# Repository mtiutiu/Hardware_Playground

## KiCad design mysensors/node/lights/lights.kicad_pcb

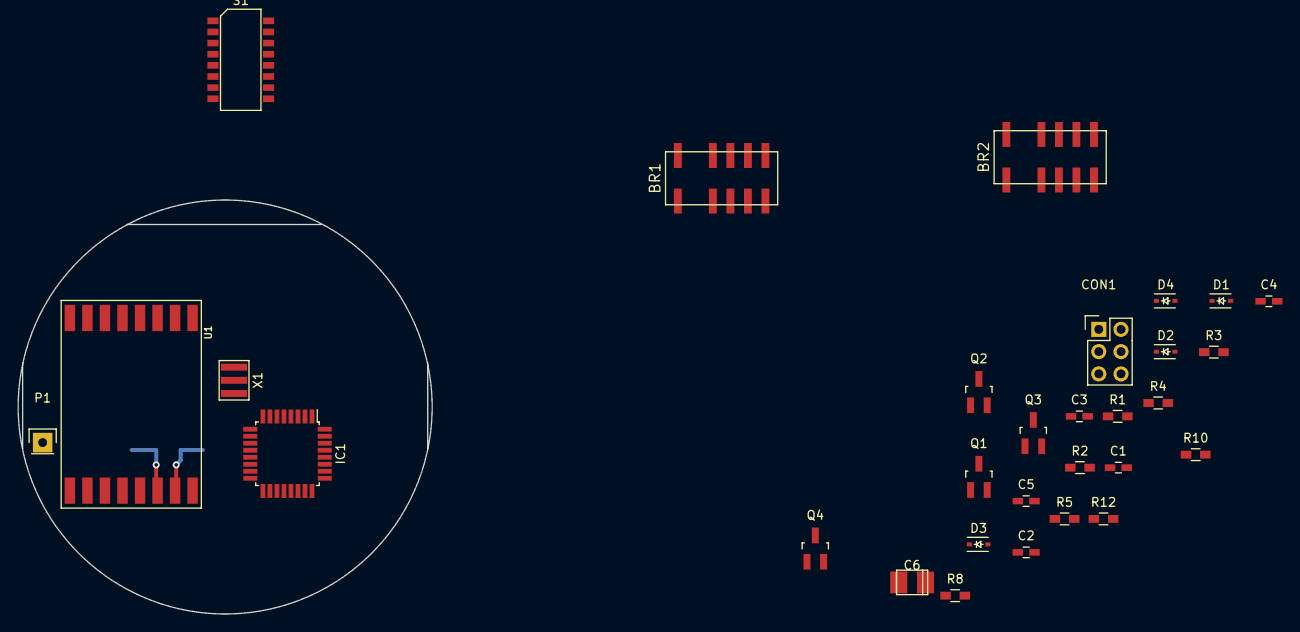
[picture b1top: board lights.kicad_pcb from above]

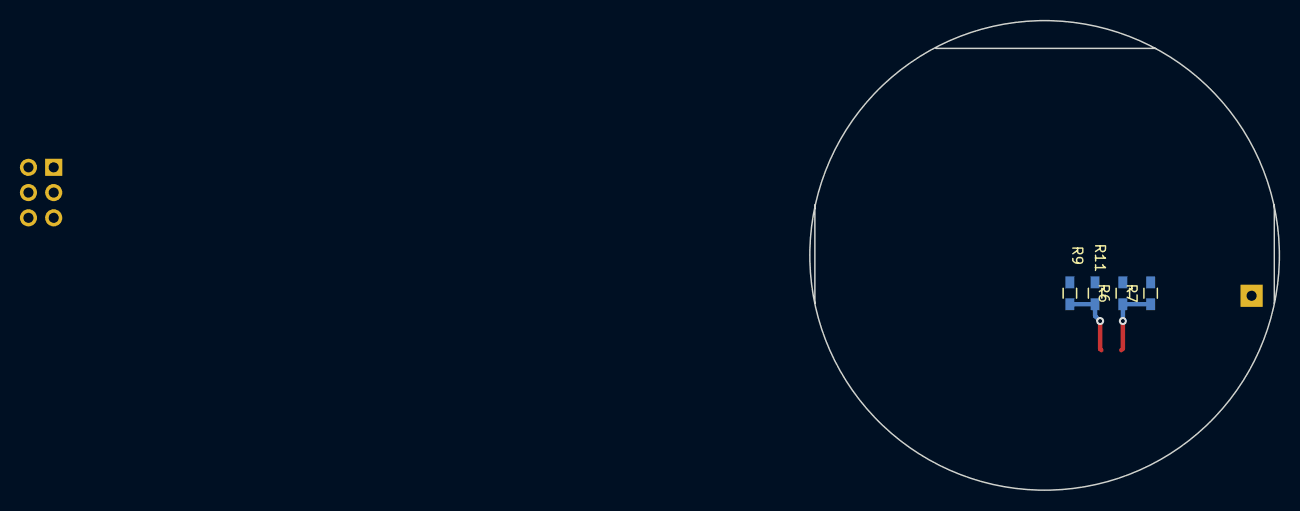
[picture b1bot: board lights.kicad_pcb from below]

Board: 2 copper layers, 47.2 x 47.2 mm, 34 parts (4 on the bottom side), 30 nets.

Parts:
BR1, BR2: V23079-E1208-B301
C1, C2, C3, C4, C5: 100n; C_0603_HandSoldering
C6: 10u; TantalC_SizeT_EIA-3528
CON1: AVR-ISP-6; Pin_Header_Straight_2x03
D1, D2, D3, D4: 1N4148; SOD-323
IC1: ATMEGA328P-A; TQFP-32_7x7mm_Pitch0.8mm
P1: ANTENNA; Pin_Header_Straight_1x01
Q1, Q2, Q3, Q4: 2n2222; SOT-23_Handsoldering
R1, R2, R3, R5: 5K6; R_0603_HandSoldering
R4: 10K; R_0603_HandSoldering
R6, R9, R10: 4K7; R_0603_HandSoldering
R7, R11, R12: 9K1; R_0603_HandSoldering
R8: 470; R_0603_HandSoldering
S1: MCDHA-08TQR; DIPSWITCH_SMD_1.27-16
U1: RFM69HW; RFM69HW_SMD_Handsoldering
X1: 8MHz; ZTTCR-3

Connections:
+3V3: BR1.7, BR1.12, BR2.7, BR2.12, C1.1, C2.2, C3.2, C6.1, CON1.2, D1.1, D2.1, D3.1, D4.1, IC1.4, IC1.6, IC1.18, R4.1, U1.8
/C0: IC1.1, S1.1
/C1: IC1.2, S1.2
/C2: IC1.9, S1.3
/C3: IC1.10, S1.4
/C4: IC1.11, S1.5
/C5: IC1.12, S1.6
/C6: IC1.13, S1.7
/INT: IC1.32, U1.2
/MISO: CON1.1, IC1.16, U1.13
/MOSI: CON1.4, IC1.15, R6.2
/RESET: C5.2, CON1.5, IC1.29, R4.2
/SCK: CON1.3, IC1.17, R10.2
/SS: IC1.14, R8.1, R9.2
GND: C1.2, C2.1, C3.1, C4.1, C5.1, C6.2, CON1.6, IC1.3, IC1.5, IC1.21, Q1.3, Q2.3, Q3.3, Q4.3, R7.2, R11.2, R12.2, S1.9, S1.10, S1.11, S1.12, S1.13, S1.14, S1.15, S1.16, U1.9, U1.11, X1.3
unnamed: BR1.1, D1.2, Q1.1
unnamed: BR1.6, D2.2, Q2.1
unnamed: BR2.1, D3.2, Q3.1
unnamed: BR2.6, D4.2, Q4.1
unnamed: C4.2, IC1.20
unnamed: IC1.7, X1.2
unnamed: IC1.8, X1.1
unnamed: P1.1, U1.10
unnamed: Q1.2, R1.1
unnamed: Q2.2, R2.1
unnamed: Q3.2, R3.1
unnamed: Q4.2, R5.1
unnamed: R6.1, R7.1, U1.14
unnamed: R10.1, R12.1, U1.12
unnamed: R9.1, R11.1, U1.15

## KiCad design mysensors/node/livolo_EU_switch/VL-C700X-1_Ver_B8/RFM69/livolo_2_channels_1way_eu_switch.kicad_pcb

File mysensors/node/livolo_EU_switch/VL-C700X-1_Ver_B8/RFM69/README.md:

## Mysensors RFM69 Livolo 2 channels 1 way EU switch front module
More details here: https://www.openhardware.io/view/306

##### 3D renderings of pcb

Top view | Bottom view
------------ | -------------
 | 

**Description:**

This is a Mysensors replica of the Livolo EU Switch(2 channels 1 way) front plate for the **VL-C700X-1_Ver_B8** Livolo hw revision.

**Key Features:**

 - **Capacitive touch sensing** using **TTP223** specialized IC
 - **AT25DF512C-SSHN-B** SPI flash module for OTA
 - **ATSHA204A** for signing
 - **MySensors** ready(Atmega328p + RFM69CW)
 - **DC-DC Buck converter** in combination with a **linear LDO voltage regulator** for efficient **noise cancelling**
  (the used LDO reduces a little bit the Buck's converter current capability - down to 150mA from 600mA but this is not important as the whole board takes about 60mA at peak)

**Work progress:**
 1. Identify the 12V line from the Livolo power/relays board - **DONE**
 2. Add **AT25DF512C-SSHN-B** SPI Flash module for OTA and **ATSHA204A** for signing - **DONE**
 3. Test/verify the pcb board correctness(from both electrical and mechanical point of views) - **DONE**
 4. Produce the initial PCB's using some external PCB manufacturer - **DONE**
 5. Components assembly(soldering) - **DONE**
 6. Create Mysensors sketch code - **DONE**
 7. Verify the real board with running code - **DONE**
 8. Verify OTA - **DONE**

Regarding point 1. from above: the EU variant that I have(VL-C700X-1 Ver: B8) doesn't expose the 12V line unfortunately. So I see 2 options here:

1. Bypass the 3V regulator from the power supply/relays board completely so that I get 12V directly to my board
2. ~~Find a free(if available) pin on the 2x6 pin connector and solder a wire to that pin from the 12V line(this requires less intervention)~~

One another thing that I noticed is that the relays are bistable so I modified the schematic/pcb to accommodate that(the relays used on my livolo switch are: **HFE60 12-1HST-L2** ( **2 coils latching, 1 Form A** as per datasheet: http://www.hongfa.com/pro/pdf/HFE60_en.pdf).

**HW Revisions:**
 - 0.1 - added SPI flash for OTA and signing support
 - 0.2 - fixed SPI slave select lines for flash and radio module
 - 0.3 - added ATSHA204A pull-up resistor
 - 0.4 - fixed leds orientation and added touch pads silkscreen
 - 0.5 - added tantalum caps for better power supply and radio stability(removed MCU reset pin cap)

The only thing I ask if using this project is to at least mention my name and if I don't ask too much you can also support my effort using the below button. Thanks.

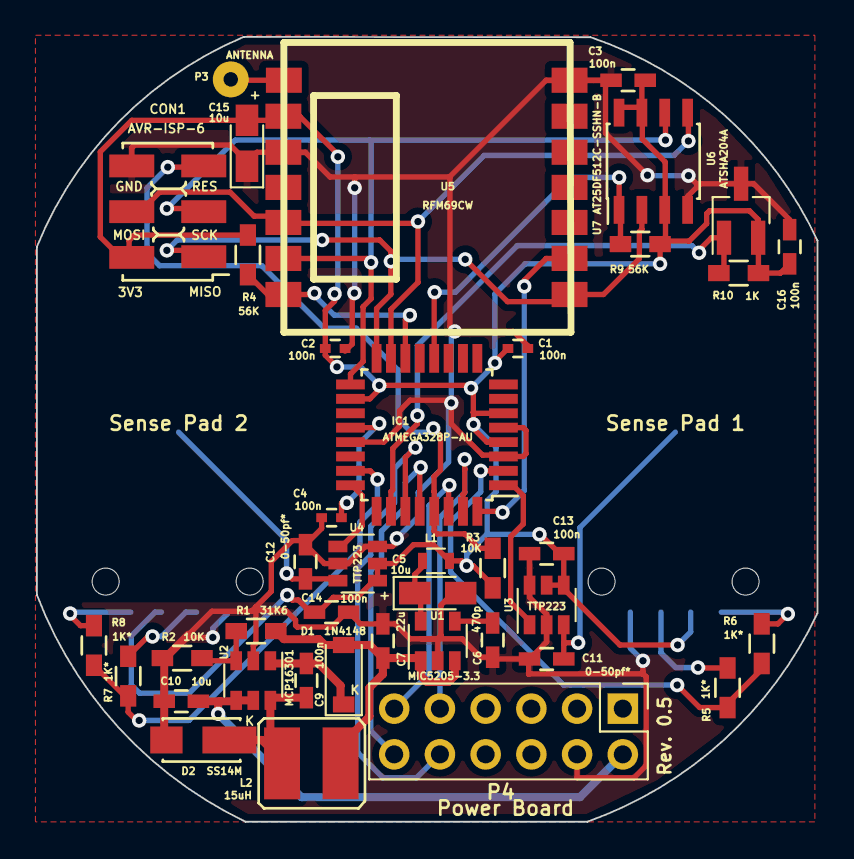
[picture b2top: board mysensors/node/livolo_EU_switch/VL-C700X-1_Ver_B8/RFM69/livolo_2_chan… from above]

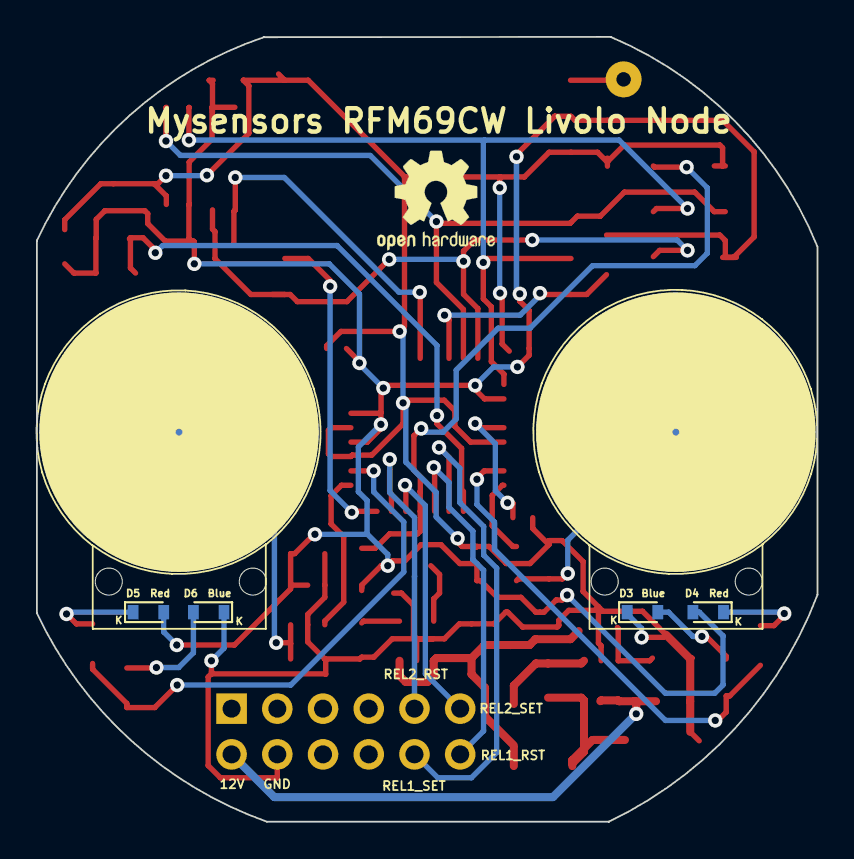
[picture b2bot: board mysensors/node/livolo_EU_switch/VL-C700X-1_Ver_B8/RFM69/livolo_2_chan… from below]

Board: 2 copper layers, 43.4 x 43.6 mm, 46 parts (4 on the bottom side), 33 nets.

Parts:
C1, C2, C4: 100n; C_0402
C3, C9, C13, C14, C16: 100n; C_0603_HandSoldering
C5, C15: 10u; CP_Tantalum_Case-R_EIA-2012-12_Wave
C6: 470p; C_0603_HandSoldering
C7: 22u; C_0603_HandSoldering
C10: 10u; C_0603_HandSoldering
C11, C12: 0-50pf*; C_0603_HandSoldering
CON1: AVR-ISP-6; AVR_ISP_SMT_Small_02x03
D1: 1N4148; SOD-123
D2: SS14M
D3, D6: Blue; D_0603
D4, D5: Red; D_0603
IC1: ATMEGA328P-AU; TQFP-32_7x7mm_Pitch0.8mm
L1: BLM18HE152SN1D; R_0603
L2: 15uH; VLCF4020T-150MR68
P1: Sense Pad 1; touch_pad_16mm
P2: Sense Pad 2; touch_pad_16mm
P3: ANTENNA; SolderWirePad_single_0-8mmDrill
P4: Power Board; Pin_Header_Straight_2x06_Pitch2.54mm
R1: 31K6; R_0603_HandSoldering
R2, R3: 10K; R_0603_HandSoldering
R4, R9: 56K; R_0603_HandSoldering
R5, R6, R7, R8: 1K*; R_0603_HandSoldering
R10: 1K; R_0603_HandSoldering
U1: MIC5205-3.3; SOT-23-5
U2: MCP16301; SOT-23-6
U3, U4: TTP223; SOT-23-6
U5: RFM69CW
U6: AT25DF512C-SSHN-B; SOIC-8_3.9x4.9mm_Pitch1.27mm
U7: ATSHA204A; SOT-23_Handsoldering

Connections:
+3V3: C1.1, C2.2, C3.2, C13.1, C14.1, C15.2, C16.2, CON1.2, D4.2, D5.2, IC1.4, IC1.6, IC1.18, L1.1, R3.1, R4.2, R9.1, R10.1, U3.4, U3.5, U4.4, U4.5, U5.2, U6.3, U6.7, U6.8, U7.2
/12Vcc: C10.1, P4.2, U2.4, U2.5
/ATSHA204A: IC1.26, R10.2, U7.1
/FLASH_SS: IC1.12, R9.2, U6.1
/INT: IC1.32, U5.9
/MISO: CON1.1, IC1.16, U5.8, U6.2
/MOSI: CON1.4, IC1.15, U5.5, U6.5
/RADIO_SS: IC1.14, R4.1, U5.7
/RESET: CON1.5, IC1.29, R3.2
/Relay1_Reset: IC1.28, P4.12
/Relay1_Set: IC1.27, P4.10
/Relay2_Reset: IC1.31, P4.9
/Relay2_Set: IC1.30, P4.11
/S1_LEDs: IC1.2, R5.2, R6.2
/S2_LEDs: IC1.23, R7.2, R8.2
/SCK: CON1.3, IC1.17, U5.6, U6.6
/TS1: IC1.1, U3.1
/TS2: IC1.24, U4.1
GND: C1.2, C2.1, C3.1, C4.1, C5.2, C6.2, C7.2, C10.2, C11.2, C12.2, C13.2, C14.2, C15.1, C16.1, CON1.6, D2.2, D3.1, D6.1, IC1.3, IC1.5, IC1.21, P4.4, R2.1, U1.2, U2.2, U3.2, U3.6, U4.2, U4.6, U5.3, U5.14, U6.4, U7.3
unnamed: C4.2, IC1.20
unnamed: C5.1, L1.2, U1.5
unnamed: C6.1, U1.4
unnamed: C7.1, D1.2, L2.1, R1.2, U1.1, U1.3
unnamed: C9.1, D1.1, U2.1
unnamed: C9.2, D2.1, L2.2, U2.6
unnamed: C11.1, P1.1, U3.3
unnamed: C12.1, P2.1, U4.3
unnamed: D3.2, R7.1
unnamed: D4.1, R8.1
unnamed: D5.1, R6.1
unnamed: D6.2, R5.1
unnamed: P3.1, U5.1
unnamed: R1.1, R2.2, U2.3

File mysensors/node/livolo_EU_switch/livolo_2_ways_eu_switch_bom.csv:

Component,Description,Part,References,Value,Footprint,Quantity Per PCB,Datasheet,Rating,Vendor,Part No
1,Unpolarized capacitor,C_Small,C11 C12,0-50pf*,C_0603_HandSoldering,2,http://www.farnell.com/datasheets/1825496.pdf,C0G/25V,Multicomp,MCMT18N100F250CT
2,Unpolarized capacitor,C_Small,C1 C2 C4,100n,C_0402,3,http://www.farnell.com/datasheets/1870456.pdf,X5R/25V,Multicomp,MC0402X104K250CT
3,Unpolarized capacitor,C_Small,C3 C9 C13 C14 C16,100n,C_0603_HandSoldering,5,http://www.farnell.com/datasheets/1901289.pdf,X7R/25V,Multicomp,MC0603B104K250CT
4,Unpolarized capacitor,C_Small,C10,10u,C_0603_HandSoldering,1,http://www.farnell.com/datasheets/2163235.pdf,X5R/25V,Murata,ZRB18AR61E106ME01L
5,Polarised capacitor,CP1_Small,C5 C15,10u,CP_Tantalum_Case-R_EIA-2012-12_Wave,2,http://www.farnell.com/datasheets/1955682.pdf,X5R/10V,Murata,GRM188R61A106KE69D
6,Unpolarized capacitor,C_Small,C7,22u,C_0603_HandSoldering,1,http://www.farnell.com/datasheets/2047978.pdf,X5R/10V,Murata,GRM188R61A226ME15D
7,Unpolarized capacitor,C_Small,C6,470p,C_0603_HandSoldering,1,http://www.farnell.com/datasheets/1870456.pdf,X7R/25V,Multicomp,MC0603B103K250CT
8,"Standard IDC6 Male Connector, ATMEL ISP 6pin",AVR-ISP-6,CON1,AVR-ISP-6,AVR_ISP_SMT_Small_02x03,1,,,,
9,"Diode, small symbol",D_Small,D1,1N4148,SOD-123,1,http://www.farnell.com/datasheets/2099776.pdf,100V/300mA,Diodes Inc.,1N4148W-7-F
10,"LED, small symbol",LED_Small,D3 D6,Blue,D_0603,2,http://www.tme.eu/ro/Document/2ff6cd49d353fcb76ded3ea208e0eb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,2.5-3.4V/5mA,Optosupply,OSB50603C1E
11,"LED, small symbol",LED_Small,D4 D5,Red,D_0603,2,http://www.tme.eu/ro/Document/2ff6cd49d353fcb76ded3ea208e0eb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,1.6-2.4V/5mA,Optosupply,OSR50603C1E
12,"Schottky diode, small symbol",D_Schottky_Small,D2,SS14M,SS14M,1,http://www.farnell.com/datasheets/1692176.pdf,40V/1A,Taiwan Semiconductor,SS14M
13,"TQFP32, 16k Flash, 1kB SRAM, 512B EEPROM",ATMEGA328P-AU,IC1,ATMEGA328P-AU,TQFP-32_7x7mm_Pitch0.8mm,1,http://www.atmel.com/images/atmel-8271-8-bit-avr-microcontro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,,,
14,"Inductor, small symbol",L_Small,L2,15uH,VLCF4020T-150MR68,1,http://www.farnell.com/datasheets/2041203.pdf,1A,TDK,VLCF4020T-150MR68
15,"Inductor, small symbol",L_Small,L1,BLM18HE152SN1D,R_0603,1,http://www.murata.com/en-us/products/productdata/87967415992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,,,
17,"Connector, double row, 02x06, pin header",CONN_02X06,P4,Power Board,Pin_Header_Straight_2x06_Pitch2.54mm,1,http://www.tme.eu/ro/Document/dd1ceac14413aeeec818bc9967f247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,,Ninigi,ZL262-12DG
20,"Resistor, small symbol",R_Small,R2 R3,10K,R_0603_HandSoldering,2,http://www.farnell.com/datasheets/2007183.pdf,50V/200mW,TE Connectivity,CRGH0603J10K
21,"Resistor, small symbol",R_Small,R10,1K,R_0603_HandSoldering,1,http://www.farnell.com/datasheets/1849611.pdf,50V/100mW,Multicomp,MCWR06X5602FTL
22,"Resistor, small symbol",R_Small,R5 R6 R7 R8,1K*,R_0603_HandSoldering,4,http://www.farnell.com/datasheets/1849611.pdf,50V/100mW 50V/200mW,Multicomp,MCWR06X1001FTL
23,"Resistor, small symbol",R_Small,R1,31K6,R_0603_HandSoldering,1,http://www.farnell.com/datasheets/1849611.pdf,50V/200mW,Multicomp,MCWR06X3162FTL
24,"Resistor, small symbol",R_Small,R4 R9,56K,R_0603_HandSoldering,2,http://www.farnell.com/datasheets/2007183.pdf,50V/200mW 50V/100mW,TE Connectivity Multicomp,CRGH0603J10K MCWR06X5602FTL
25,"AT25DF512C, 512-Kbit SPI Serial Flash Memory, SOIC-8, Vcc=3.3V",AT25DF512C,U6,AT25DF512C-SSHN-B,SOIC-8_3.9x4.9mm_Pitch1.27mm,1,http://www.adestotech.com/wp-content/uploads/DS-AT25DF512C-030.pdf,,,
26,"ATSHA204A, Secure Authentication and Validation Device, SOT-23, Vcc=3.3V",ATSHA204A,U7,ATSHA204A,SOT-23_Handsoldering,1,http://www.atmel.com/Images/Atmel-8885-CryptoAuth-ATSHA204A-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,,,
27,"4.0 to 30V Input, 1A output, integrated switch step-down regulator, SOT-23-6 package",MCP16301,U2,MCP16301,SOT-23-6,1,http://www.farnell.com/datasheets/2129968.pdf,4-30V/3.3V/600mA,Microchip,MCP16301T-I/CHY
28,,MIC5205-3.3YM5TR,U1,MIC5205-3.3,SOT-23-5,1,http://www.farnell.com/datasheets/29605.pdf,3.3V/150mA,Microchip,MIC5205-3.3YM5-TR
29,,RFM69CW,U5,RFM69CW,RFM69CW,1,http://www.hoperf.com/upload/rf/RFM69CW-V1.1.pdf,3.3V/868MHz,HopeRF,RFM69CW
30,,TTP223,U3 U4,TTP223,SOT-23-6,2,http://www.coldtears-electronics.com/images/TTP223.pdf,,Tontek,
,,,,,,,,,,
,,,,,,,,,,
,,,,,,,,,,
,,,,,,,,,,
,,,,,,,,,,
Component Groups:,30,,,,,,,,,
Component Count:,43,,,,,,,,,
Fitted Components:,43,,,,,,,,,
Number of PCBs:,1,,,,,,,,,
Total components:,43,,,,,,,,,
Schematic Version:,0.5,,,,,,,,,
Schematic Date:,,,,,,,,,,
BoM Date:,Mon 13 Mar 2017 05:45:51 PM EET,,,,,,,,,
Schematic Source:,/home/mtiutiu/Work/kicad/mysensors/node/livolo_EU_switch/livolo_2_ways_eu_switch.sch,,,,,,,,,
KiCad Version:,Eeschema no-vcs-found-5e5259b~58~ubuntu16.04.1,,,,,,,,,

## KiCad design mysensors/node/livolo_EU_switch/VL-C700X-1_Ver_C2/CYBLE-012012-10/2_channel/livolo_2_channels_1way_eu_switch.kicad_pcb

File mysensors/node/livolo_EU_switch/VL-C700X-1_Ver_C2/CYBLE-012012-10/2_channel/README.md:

## Mysensors PSOC PROC BLE (CYBLE-012012-10) Livolo 2 channels 1 way EU switch front module

##### 3D renderings of pcb

Top view | Bottom view
------------ | -------------
 | 

If this project was of any help you can buy me a beer or at least support my effort by using the below button. Thanks.

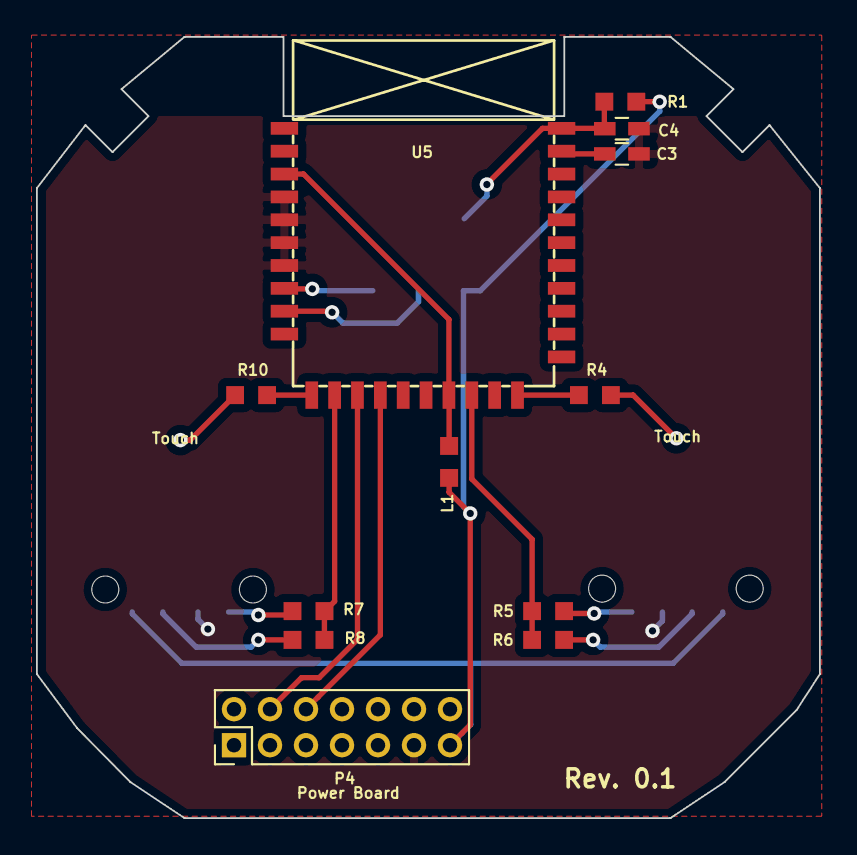
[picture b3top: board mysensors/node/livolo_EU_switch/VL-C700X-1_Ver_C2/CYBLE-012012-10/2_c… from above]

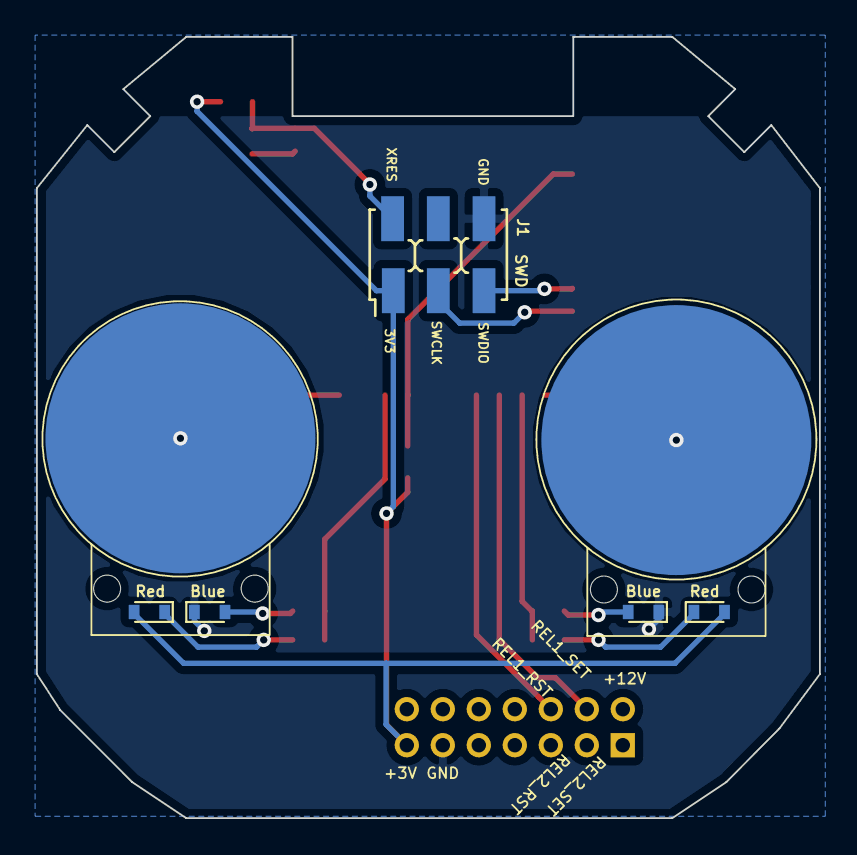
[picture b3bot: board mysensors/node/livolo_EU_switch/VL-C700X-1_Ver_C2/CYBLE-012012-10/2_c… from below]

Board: 2 copper layers, 43.5 x 43.4 mm, 19 parts (5 on the bottom side), 21 nets.

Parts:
C3: 2n2; C_0603_HandSoldering
C4: 100p; C_0603_HandSoldering
D3, D6: Blue; D_0603
D4, D5: Red; D_0603
J1: SWD; AVR_ISP_SMT_Small_02x03
L1: 300ohm/100Mhz; R_0603_1608Metric_Pad0.99x1.00mm_HandSolder
P4: Power Board; Pin_Header_Straight_2x07_Pitch2.00mm
R1, R4, R10: 4K7; R_0603_1608Metric_Pad0.99x1.00mm_HandSolder
R5, R6, R7, R8: 1K*; R_0603_1608Metric_Pad0.99x1.00mm_HandSolder
U1: Touch; livolo_ts_guard_cut_left
U5: CYBLE-012012-10
U6: Touch; livolo_ts_guard_cut_right

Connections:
+3V3: D4.2, D5.2, J1.1, L1.1, P4.13, R1.2
/Relay1_Reset: P4.6, U5.18
/Relay1_Set: P4.4, U5.19
/Relay2_Reset: P4.3, U5.17
/Relay2_Set: P4.5, U5.16
/S1_LEDs: R5.2, R6.2, U5.14
/S2_LEDs: R7.2, R8.2, U5.20
/SWCLK: J1.3, U5.23
/SWDIO: J1.5, U5.24
/TS1: R10.2, U5.21
/TS2: R4.1, U5.12
/XRES: C4.1, J1.2, R1.1, U5.1
GND: C3.1, C4.2, D3.1, D6.1, J1.6, P4.11, U5.25, U5.26, U5.27, U5.28
unnamed: C3.2, U5.2
unnamed: D3.2, R7.1
unnamed: D4.1, R8.1
unnamed: D5.1, R6.1
unnamed: D6.2, R5.1
unnamed: L1.2, U5.15, U5.29
unnamed: R4.2, U6.1
unnamed: R10.1, U1.1

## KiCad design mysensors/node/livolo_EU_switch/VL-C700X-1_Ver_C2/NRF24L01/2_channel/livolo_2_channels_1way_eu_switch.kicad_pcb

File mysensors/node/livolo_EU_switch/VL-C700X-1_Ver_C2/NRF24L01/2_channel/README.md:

## Mysensors NRF24L01 Livolo 2 channels 1 way EU switch front module

##### 3D renderings of pcb

Top view | Bottom view
------------ | -------------
 | 

**Description:**

This is a Mysensors replica of the Livolo EU Switch(2 channels 1 way) front plate for the **VL-C702X-2_Ver_C1** Livolo hw revision.

**Key Features:**

 - **Capacitive touch sensing** using **MTCH105** specialized IC
 - **ATSHA204A** for signing
 - **MCP9700** for temperature sensing
 - **MySensors** ready(Atmega328p + NRF24L01)

**Work progress:**
 1. Test/verify the pcb board correctness(from both electrical and mechanical point of views) - **DONE**
 2. Produce the initial PCB's using some external PCB manufacturer - **IN PROGRESS**
 3. Components assembly(soldering)
 4. Create Mysensors sketch code
 5. Verify the real board with running code
 6. Verify OTA

**HW Revisions:**
 - 0.1 - initial hw design
 - 0.2 - switched to MTCH105 touch IC and added temperature sensor

If this project was of any help you can buy me a beer or at least support my effort by using the below button. Thanks.

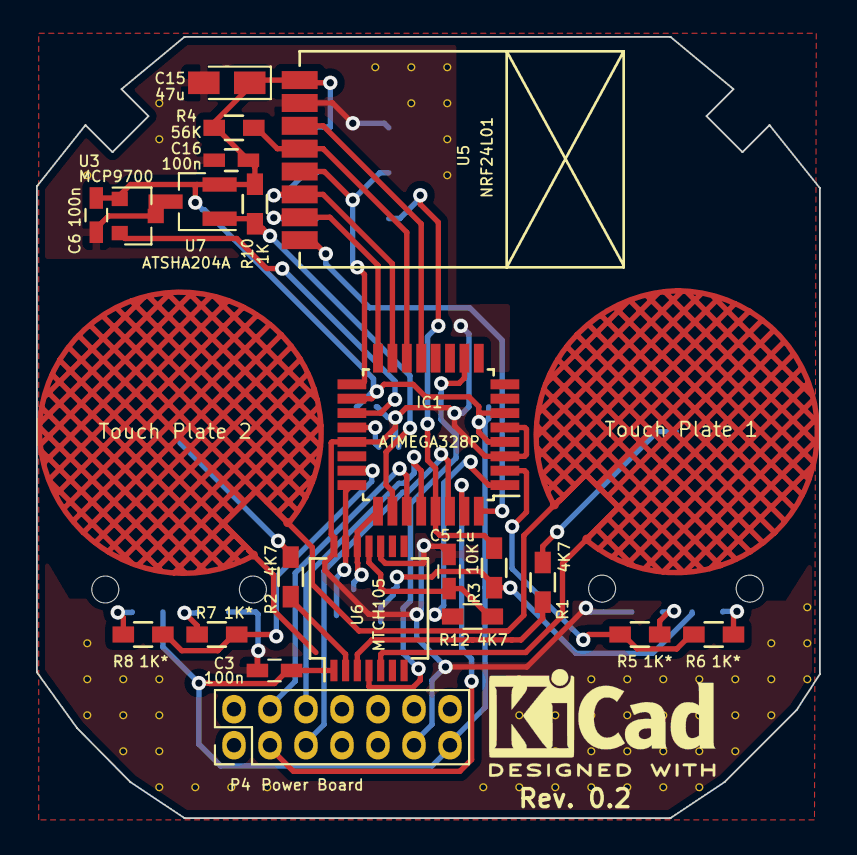
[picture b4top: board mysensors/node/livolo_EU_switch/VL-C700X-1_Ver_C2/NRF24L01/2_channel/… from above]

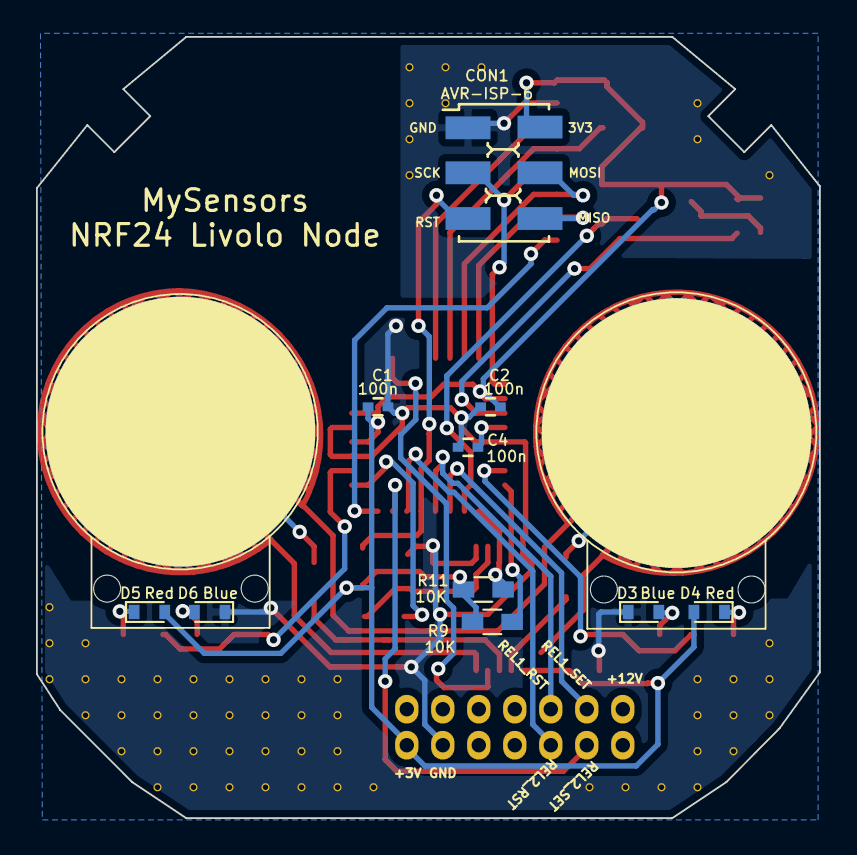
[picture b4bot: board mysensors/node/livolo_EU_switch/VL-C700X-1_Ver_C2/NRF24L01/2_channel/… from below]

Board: 2 copper layers, 43.5 x 43.4 mm, 90 parts (10 on the bottom side), 32 nets.

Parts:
C1, C2, C4: 100n; C_0402
C3, C6, C16: 100n; C_0603_HandSoldering
C5: 1u; C_0603_HandSoldering
C15: 47u; CP_Tantalum_Case-R_EIA-2012-12_Wave
CON1: AVR-ISP-6; AVR_ISP_SMT_Small_02x03
D3, D6: Blue; D_0603
D4, D5: Red; D_0603
IC1: ATMEGA328P; TQFP-32_7x7mm_Pitch0.8mm
P4: Power Board; Pin_Header_Straight_2x07_Pitch2.00mm
R1, R2, R12: 4K7; R_0603_HandSoldering
R3, R9, R11: 10K; R_0603_HandSoldering
R4: 56K; R_0603_HandSoldering
R5, R6, R7, R8: 1K*; R_0603_HandSoldering
R10: 1K; R_0603_HandSoldering
U1: Touch Plate 2; livolo_ts_guard_cut_simple
U2: Touch Plate 1; livolo_ts_guard_cut_simple
U3: MCP9700; SOT-23
U5: NRF24L01; NRF24L01-SMD
U6: MTCH105; SSOP-14_5.3x6.2mm_Pitch0.65mm
U7: ATSHA204A; SOT-23_Handsoldering
V2_4, V2_17, V2_18, V2_19, V3_18, V3_19, V3_20, V4_2, V4_3, V4_18, V4_19, V4_20, V4_21, V5_21, V6_21, V7_21, V10_1, V11_1, V11_2, V12_1, V12_2, V12_3, V12_4, V13_21, V14_18, V14_19, V14_20, V14_21, V15_18, V15_19, V15_20, V15_21, V16_18, V16_19, V16_20, V16_21, V17_18, V17_19, V17_20, V17_21, V18_18, V18_19, V18_20, V18_21, V19_18, V19_19, V19_20, V19_21, V20_18, V20_19, V20_20, V21_17, V21_18, V21_19, V22_16, V22_17, V22_18: AUTO_VIA; VIA_MATRIX

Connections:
+3V3: C1.1, C2.2, C3.1, C6.2, C15.1, C16.2, CON1.2, D4.2, D5.2, IC1.4, IC1.6, IC1.18, P4.13, R3.1, R4.2, R9.1, R10.1, R11.1, U3.1, U5.2, U6.1, U7.2
/ATSHA204A: IC1.26, R10.2, U7.1
/MISO: CON1.6, IC1.16, U5.7
/MOSI: CON1.4, IC1.15, U5.6
/MTPM: IC1.10, U6.4
/MTSA: IC1.1, R12.1
/RADIO_CE: IC1.13, U5.3
/RADIO_CSN: IC1.14, R4.1, U5.4
/RADIO_IRQ: IC1.32, U5.8
/RESET: CON1.5, IC1.29, R3.2
/Relay1_Reset: IC1.28, P4.6
/Relay1_Set: IC1.27, P4.4
/Relay2_Reset: IC1.31, P4.3
/Relay2_Set: IC1.30, P4.5
/S1_LEDs: IC1.2, R5.2, R6.2
/S2_LEDs: IC1.23, R7.2, R8.2
/SCK: CON1.3, IC1.17, U5.5
/TEMP_SENS: IC1.19, U3.2
/TS1: IC1.24, R9.2, U6.13
/TS2: IC1.25, R11.2, U6.12
GND: C1.2, C2.1, C3.2, C4.1, C5.2, C6.1, C15.2, C16.1, CON1.1, D3.1, D6.1, IC1.3, IC1.5, IC1.21, P4.11, U3.3, U5.1, U6.10, U6.14, U7.3, V2_4.1, V2_17.1, V2_18.1, V2_19.1, V3_18.1, V3_19.1, V3_20.1, V4_2.1, V4_3.1, V4_18.1, V4_19.1, V4_20.1, V4_21.1, V5_21.1, V6_21.1, V7_21.1, V10_1.1, V11_1.1, V11_2.1, V12_1.1, V12_2.1, V12_3.1, V12_4.1, V13_21.1, V14_18.1, V14_19.1, V14_20.1, V14_21.1, V15_18.1, V15_19.1, V15_20.1, V15_21.1, V16_18.1, V16_19.1, V16_20.1, V16_21.1, V17_18.1, V17_19.1, V17_20.1, V17_21.1, V18_18.1, V18_19.1, V18_20.1, V18_21.1, V19_18.1, V19_19.1, V19_20.1, V19_21.1, V20_18.1, V20_19.1, V20_20.1, V21_17.1, V21_18.1, V21_19.1, V22_16.1, V22_17.1, V22_18.1
unnamed: C4.2, IC1.20
unnamed: C5.1, R12.2, U6.11
unnamed: D3.2, R7.1
unnamed: D4.1, R8.1
unnamed: D5.1, R6.1
unnamed: D6.2, R5.1
unnamed: R1.1, U6.3
unnamed: R1.2, U2.1
unnamed: R2.1, U1.1
unnamed: R2.2, U6.2
unnamed: U1.2, U2.2, U6.5

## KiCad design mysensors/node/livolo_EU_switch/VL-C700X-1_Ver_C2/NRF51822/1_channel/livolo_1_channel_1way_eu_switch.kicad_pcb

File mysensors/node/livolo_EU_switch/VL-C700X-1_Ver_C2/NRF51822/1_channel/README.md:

## Mysensors NRF51822 Livolo 1 channels 1 way EU switch front module

##### 3D renderings of pcb

Top view | Bottom view
------------ | -------------
 | 

**Description:**

This is a Mysensors replica of the Livolo EU Switch(1 channel 1 way) front plate for the **VL-C702X-2_Ver_C1** Livolo hw revision.

**Key Features:**

 - **Capacitive touch sensing** using **MTCH102** specialized IC
 - **MySensors** ready(NRF51822)
 - **DC-DC Buck converter** for powering from the 12V line ( the DC-DC converter can be bypassed and not used at all if desired by soldering the **3V_EN** jumper and removing the L1 ferrite bead or by not soldering the dc-dc converter components)

**Firmware programming and testing steps for MySensors:**
1. Install Arduino IDE
2. Install nrf5 arduino core from here: https://github.com/sandeepmistry/arduino-nRF5
3. Select the **nrf51 generic board (16K ram and 256K flash)** variant(or nrf52 generic if you have a nrf52832 device)
4. The low frequency oscillator needs to be set to **RC oscillator** in the Arduino menu
5. **NO Softdevice** needs to be selected
6. Use a st-link v2 programmer
7. You need to connect only: SWD, SWCLK, Vdd and GND
8. Load your MySensors sketch or use the one provided with this project 

**Firmware programming and testing steps for BLE:**
1. Install Arduino IDE
2. Install nrf5 arduino core from here: https://github.com/sandeepmistry/arduino-nRF5
3. install Arduino ble peripheral library from here: https://github.com/sandeepmistry/arduino-BLEPeripheral
4. Install the required softdevice as explained here: https://github.com/sandeepmistry/arduino-nRF5#selecting-a-softdevice
5. Select the **nrf51 generic board (16K ram and 256K flash)** variant(or nrf52 generic if you have a nrf52832 device)
6. The low frequency oscillator needs to be set to **RC oscillator** in the Arduino menu
7. Select **S130** softdevice from menu if you have nrf51(or S132 if you have nrf52)
8. Use a st-link v2 programmer
9. You need to connect only: SWD, SWCLK, Vdd and GND
10. Load my BLE testing sketch, compile and upload
11. Use the nrf connect tool for Android: https://play.google.com/store/apps/details?id=no.nordicsemi.android.mcp&hl=en
12. Scan for available devices - you should see a "Livolo Lights" device
13. Connect to it
14. After connecting and characteristics discovery -> expand one of the "unknown characteristic"(there's one for each livolo channel or relay)
15. Use the button with an UP arrow on it to send values - select **UINT8** - send 1 for turning ON the light, send 0 for turning OFF the light for the selected channel

**Extra steps needed for the Livolo power supply/relays board!!!**
 1. The R3 resistor(marked with 104 - 100Kohm) near the bridge rectifier needs to be replaced with a 1Kohm one(1206 package)
 2. The R13 SMD resistor needs to be replaced with a solder bridge
 3. Mount a X2 capacitor of 1uF - 2.2uF rated at a minimum of 275Vac directly on the light bulb(in parallel)

**Notes:**
 - If using BLE based firmware with this board the current consumption on average is only **5mA **for the **WHOLE BOARD**(including leds) and this is **constant** over time
 - If using MySensors firmware instead the current consumption on average increases to **18-20mA **which is 4 times bigger than BLE
 - What I noticed is that the original Livolo power supply(the one used in stand-by mode) is designed to work with currents of 1mA or even below so that's why the above hardware modifications(the extra steps) need to be performed - otherwise the switch won't start
 - It's not advised to replace the R3 resistor with a bridge only as the stand-by power supply may be damaged over time and it's required that the custom top board(for which the current project was made for) to draw a lower current as much as possible(ideally would be several milliamps and even lower but it works with 10-20mA also)

**Practical usage ideas:**
 - Currently(and based on my previous experience with this kind of project) I will use all the Livolo switches preloaded with BLE firmware because of the lower current consumption AND in each room there will be a BLE Central node(based on Raspberry PI Zero W) - see this project: [RFM69W Raspberry PI Zero(W) Shield(HAT)](https://www.openhardware.io/view/487/RFM69W-Raspberry-PI-ZeroW-ShieldHAT) which will route messages to/from the Livolo switches BLE Peripherals to the MySensors network.

**HW Revisions:**
 - 0.1 - initial hw design
 - 0.2 - switched to MTCH102 touch sensor
 - 0.3 - added 3V line jumper

If this project was of any help you can buy me a beer or at least support my effort by using the below button. Thanks.

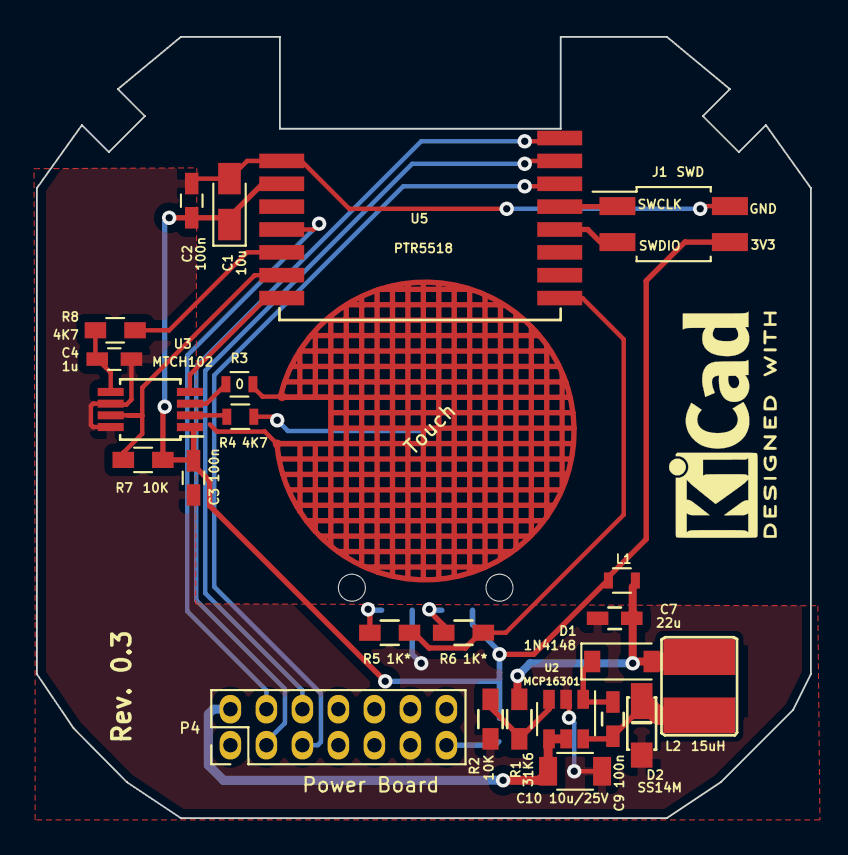
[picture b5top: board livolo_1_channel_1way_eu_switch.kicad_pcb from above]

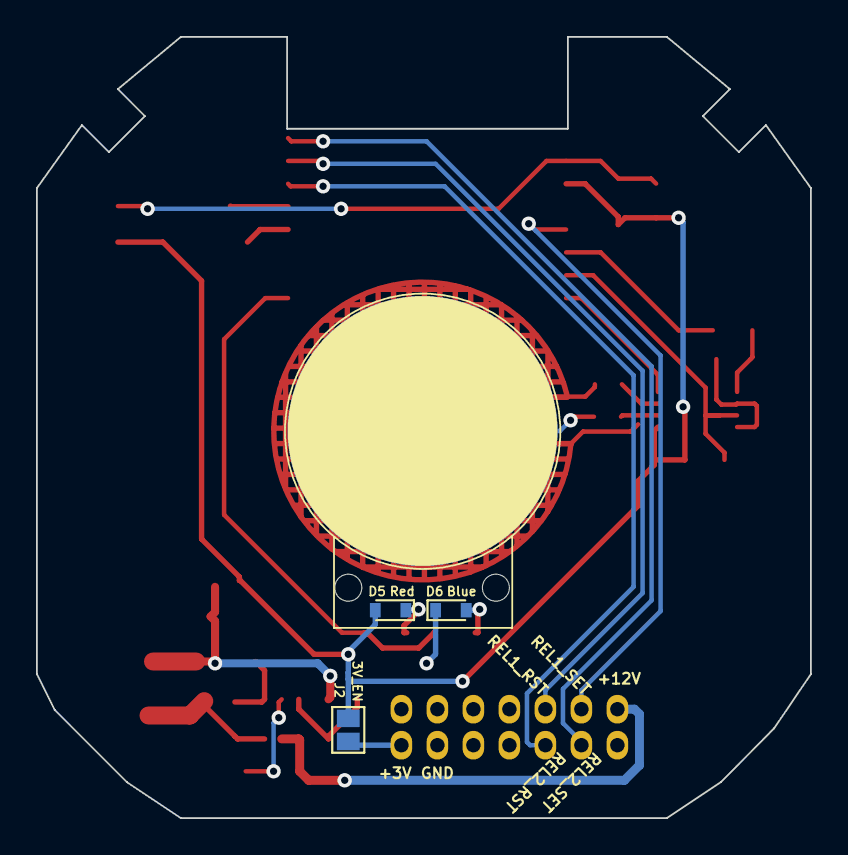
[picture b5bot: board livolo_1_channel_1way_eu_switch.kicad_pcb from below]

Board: 2 copper layers, 43.0 x 43.4 mm, 28 parts (3 on the bottom side), 25 nets.

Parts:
C1: 10u; CP_Tantalum_Case-R_EIA-2012-12_Wave
C2, C3, C9: 100n; C_0603_HandSoldering
C4: 1u; C_0603_HandSoldering
C7: 22u; C_0603_HandSoldering
C10: 10u/25V; C_1206
D1: 1N4148; SOD-123
D2: SS14M
D5: Red; D_0603
D6: Blue; D_0603
J1: SWD; Pin_Header_Straight_2x02_Pitch2.00mm_SMD
J2: 3V_EN; GS2
L1: BLM18HE152SN1D; R_0603
L2: 15uH; VLCF4020T-150MR68
P4: Power Board; Pin_Header_Straight_2x07_Pitch2.00mm
R1: 31K6; R_0603_HandSoldering
R2, R7: 10K; R_0603_HandSoldering
R3: 0; R_0603
R4: 4K7; R_0603
R5, R6: 1K*; R_0603_HandSoldering
R8: 4K7; R_0603_HandSoldering
U1: Touch; livolo_ts_guard
U2: MCP16301; SOT-23-6
U3: MTCH102; MSOP-8_3x3mm_Pitch0.65mm
U5: PTR5518

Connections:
+3V3: C1.1, C2.2, C3.2, D5.2, J1.4, J2.2, L1.2, R7.2, U3.1, U5.10
/12Vcc: C10.1, P4.2, U2.4, U2.5
/MTPM: U3.4, U5.15
/MTSA: R8.1, U5.13
/Relay1_Reset: P4.6, U5.7
/Relay1_Set: P4.4, U5.12
/Relay2_Reset: P4.3, U5.8
/Relay2_Set: P4.5, U5.6
/S1_LEDs: R5.2, R6.2, U5.1
/SWCLK: J1.1, U5.5
/SWDIO: J1.3, U5.4
/TS1: R7.1, U3.7, U5.14
GND: C1.2, C2.1, C3.1, C4.2, C7.2, C10.2, D2.2, D6.1, J1.2, P4.11, R2.1, U2.2, U3.6, U3.8, U5.9
unnamed: C4.1, R8.2, U3.5
unnamed: C7.1, D1.2, L1.1, L2.1, R1.2
unnamed: C9.1, D1.1, U2.1
unnamed: C9.2, D2.1, L2.2, U2.6
unnamed: D5.1, R6.1
unnamed: D6.2, R5.1
unnamed: J2.1, P4.13
unnamed: R1.1, R2.2, U2.3
unnamed: R3.1, U3.3
unnamed: R3.2, U1.2
unnamed: R4.1, U3.2
unnamed: R4.2, U1.1
